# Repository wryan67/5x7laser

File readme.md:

## 5x7 laser gun

This lasergun can be produced using 5" x 7" sheets of plastic or basswood.

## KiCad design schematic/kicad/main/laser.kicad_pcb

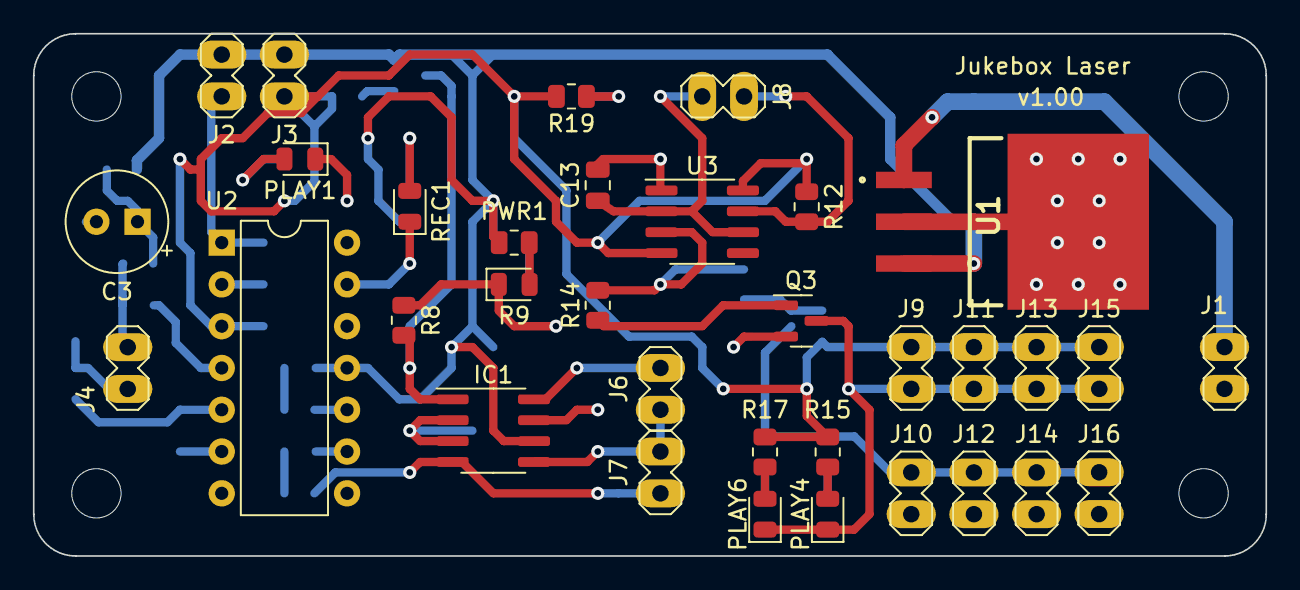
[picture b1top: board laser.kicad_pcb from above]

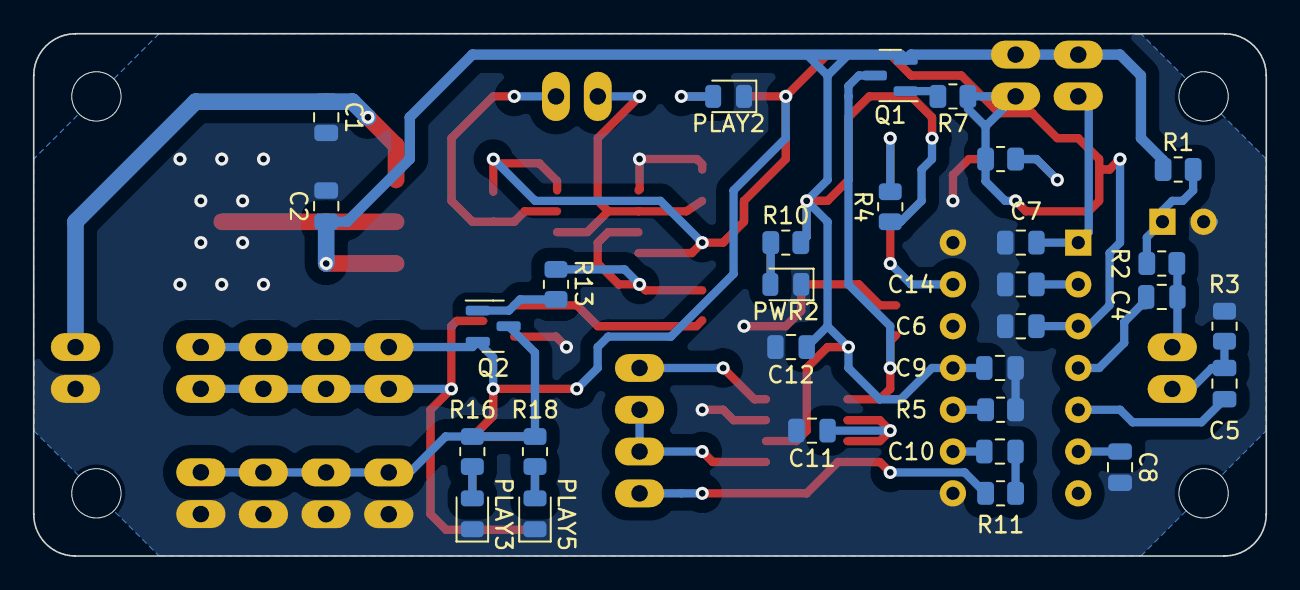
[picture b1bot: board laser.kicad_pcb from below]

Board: 2 copper layers, 74.9 x 31.8 mm, 64 parts (30 on the bottom side), 38 nets.

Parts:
C1: 334; C_0805_2012Metric
C2, C4, C5, C9: 104; C_0805_2012Metric
C3: 220 µF; CP_Radial_Tantal_D6.0mm_P2.50mm
C6, C7, C14: 102; C_0805_2012Metric
C8: 475; C_0805_2012Metric
C10: 394; C_0805_2012Metric
C11, C12: 105; C_0805_2012Metric
C13: 106; C_0805_2012Metric
IC1: LM4871MX_NOPB; LM4871
J1: Power; PinHeader_1x02_P2.54mm_Vertical_Wide
J2: Rec; PinHeader_1x02_P2.54mm_Vertical_Wide
J3: Play; PinHeader_1x02_P2.54mm_Vertical_Wide
J4: Mic; PinHeader_1x02_P2.54mm_Vertical_Wide
J6: Speaker; PinHeader_1x02_P2.54mm_Vertical_Wide
J7, J8: 100k pot; PinHeader_1x02_P2.54mm_Vertical_Wide
J9, J10, J11, J12, J13, J14, J15, J16: LED; PinHeader_1x02_P2.54mm_Vertical_Wide
PLAY1, PLAY2: Blue; LED_0805_2012Metric
PLAY3, PLAY4, PLAY5, PLAY6: Yellow; LED_0805_2012Metric
PWR1, PWR2: Green; LED_0805_2012Metric
Q1, Q2: 2PB709AXL; SOT-23
Q3: PMBT2222A; SOT-23
R1, R4, R6, R9, R10, R12, R19: 1k; R_0805_2012Metric
R2, R3: 4.7k; R_0805_2012Metric
R5: 80k; R_0805_2012Metric
R7, R13, R14: 100k; R_0805_2012Metric
R8, R11: 10k; R_0805_2012Metric
R15, R16, R17, R18: 200 Ω; R_0805_2012Metric
REC1: Red; LED_0805_2012Metric
U1: ua7805; ua7805-KTT-_R-PSFM-G3_
U2: ISD1820
U3: NE555D; SOIC-8_3.9x4.9mm_P1.27mm

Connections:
+5v: C2.1, C9.1, C12.1, IC1.6 (VDD), J2.2, J3.2, Q1.2 (E), R1.1, R4.1, R9.2, R10.2, U1.3 (OUTPUT), U2.11 (Vcc)
+9v: C1.1, J1.2, U1.1 (INPUT)
/Amplifier/SPK+: IC1.5 (VO1), J6.2, J7.1
/Amplifier/SPK-: IC1.8 (VO2), J6.1
/Jukebox/AGC: C8.1, U2.6 (AGC)
/Jukebox/M+: C4.1, U2.4 (MIC(+))
/Jukebox/M-: C5.1, U2.5 (MIC(-))
/Jukebox/PLAY_E: C14.1, U2.2 (PLAY_E)
Flasher Speed: J8.1, R12.2, U3.7 (DIS)
GND: C1.2, C2.2, C3.2, C6.2, C7.2, C8.2, C9.2, C11.2, C12.2, C13.2, C14.2, IC1.7 (GND), J1.1, J10.2, J12.2, J14.2, J16.2, PLAY1.1 (K), PLAY2.1 (K), PLAY3.1 (K), PLAY5.1 (K), PWR1.1 (K), PWR2.1 (K), Q3.2 (E), R3.2, R5.2, R8.1, U1.2 (COMMON_1), U1.4 (COMMON_2), U2.8 (VSSA), U2.14 (VSSD), U3.1 (GND)
Mic(+): C4.2, J4.2, R2.2
Mic(-): C5.2, J4.1, R3.1
unnamed: C3.1, R1.2, R2.1
unnamed: C10.2, R11.2
unnamed: C11.1, IC1.2 (BYPASS), IC1.3 (+IN)
unnamed: C13.1, J8.2, U3.2 (TR), U3.6 (THR)
unnamed: J10.1, J12.1, J14.1, J16.1, Q2.3 (C), R16.2, R18.2
unnamed: J9.2, J11.2, J13.2, J15.2, PLAY4.1 (K), PLAY6.1 (K), Q3.3 (C)
unnamed: PLAY1.2 (A), R6.1
unnamed: PLAY2.2 (A), R19.1
unnamed: PLAY3.2 (A), R16.1
unnamed: PLAY4.2 (A), R15.1
unnamed: PLAY5.2 (A), R18.1
unnamed: PLAY6.2 (A), R17.1
unnamed: PWR1.2 (A), R9.1
unnamed: PWR2.2 (A), R10.1
unnamed: Q1.1 (B), R7.2
unnamed: Q2.1 (B), R13.2
unnamed: Q3.1 (B), R14.1
unnamed: R4.2, REC1.2 (A)
unnamed: REC1.1 (K), U2.13 (RECLED)
unnamed: R5.1, U2.10 (ROSC)
unnamed: R13.1, R14.2, U3.3 (Q)
PLAY: C6.1, J3.1, J9.1, J11.1, J13.1, J15.1, Q2.2 (E), R6.2, R7.1, R12.1, R15.2, R17.2, R19.2, U2.3 (PLAY_L), U3.4 (R), U3.8 (VCC)
REC: C7.1, J2.1, U2.1 (REC)
SPK(+): C10.1, U2.9 (SPK(+))
Shutdown: IC1.1 (SHUTDOWN), Q1.3 (C), R8.2
VOL(-): IC1.4 (-IN), J7.2, R11.1

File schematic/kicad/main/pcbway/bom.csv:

"Id";"Designator";"Footprint";"Quantity";"Designation";"Supplier and ref";
1;"REC1";"LED_0805_2012Metric";1;"Red";;;
2;"J10,J16,J12,J9,J15,J11,J14,J13";"PinHeader_1x02_P2.54mm_Vertical_Wide";8;"LED";;;
3;"R8,R11";"R_0805_2012Metric";2;"10k";;;
4;"C13";"C_0805_2012Metric";1;"106";;;
5;"R17,R15,R18,R16";"R_0805_2012Metric";4;"200 Ω";;;
6;"J4";"PinHeader_1x02_P2.54mm_Vertical_Wide";1;"Mic";;;
7;"PWR1,PWR2";"LED_0805_2012Metric";2;"Green";;;
8;"IC1";"LM4871";1;"LM4871MX_NOPB";;;
9;"J1";"PinHeader_1x02_P2.54mm_Vertical_Wide";1;"Power";;;
10;"C3";"CP_Radial_Tantal_D6.0mm_P2.50mm";1;"220 µF";;;
11;"U3";"SOIC-8_3.9x4.9mm_P1.27mm";1;"NE555D";;;
12;"J2";"PinHeader_1x02_P2.54mm_Vertical_Wide";1;"Rec";;;
13;"R14,R7,R13";"R_0805_2012Metric";3;"100k";;;
14;"J3";"PinHeader_1x02_P2.54mm_Vertical_Wide";1;"Play";;;
15;"PLAY6,PLAY4,PLAY5,PLAY3";"LED_0805_2012Metric";4;"Yellow";;;
16;"U2";"ISD1820";1;"ISD1820";;;
17;"PLAY1,PLAY2";"LED_0805_2012Metric";2;"Blue";;;
18;"R12,R19,R9,R4,R1,R6,R10";"R_0805_2012Metric";7;"1k";;;
19;"J6";"PinHeader_1x02_P2.54mm_Vertical_Wide";1;"Speaker";;;
20;"U1";"ua7805-KTT-_R-PSFM-G3_";1;"ua7805";;;
21;"J7,J8";"PinHeader_1x02_P2.54mm_Vertical_Wide";2;"100k pot";;;
22;"Q3";"SOT-23";1;"PMBT2222A";;;
23;"C9,C2,C5,C4";"C_0805_2012Metric";4;"104";;;
24;"Q2,Q1";"SOT-23";2;"2PB709AXL";;;
25;"R2,R3";"R_0805_2012Metric";2;"4.7k";;;
26;"C1";"C_0805_2012Metric";1;"334";;;
27;"C12,C11";"C_0805_2012Metric";2;"105";;;
28;"C7,C6,C14";"C_0805_2012Metric";3;"102";;;
29;"C8";"C_0805_2012Metric";1;"475";;;
30;"C10";"C_0805_2012Metric";1;"394";;;
31;"R5";"R_0805_2012Metric";1;"80k";;;

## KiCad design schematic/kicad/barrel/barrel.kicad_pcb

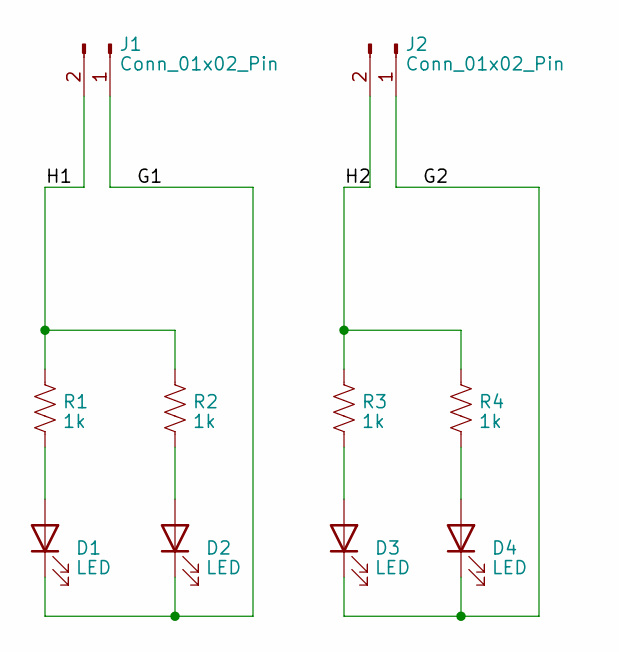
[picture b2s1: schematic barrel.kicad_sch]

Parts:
D1, D2, D3, D4: LED; LED_0805_2012Metric
J1, J2: Conn_01x02_Pin; PinHeader_1x02_P2.54mm_Vertical_Wide
R1, R2, R3, R4: 1k; R_0805_2012Metric

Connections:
/G1: D1.1 (K), D2.1 (K), J1.1
/G2: D3.1 (K), D4.1 (K), J2.1
/H1: J1.2, R1.1, R2.1
/H2: J2.2, R3.1, R4.1
unnamed: D1.2 (A), R1.2
unnamed: D2.2 (A), R2.2
unnamed: D3.2 (A), R3.2
unnamed: D4.2 (A), R4.2

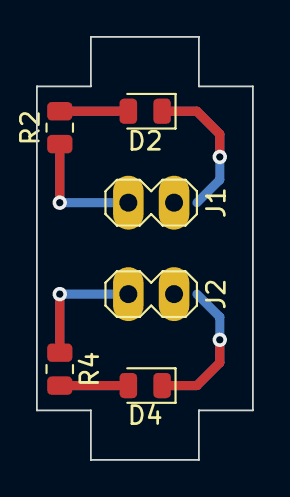
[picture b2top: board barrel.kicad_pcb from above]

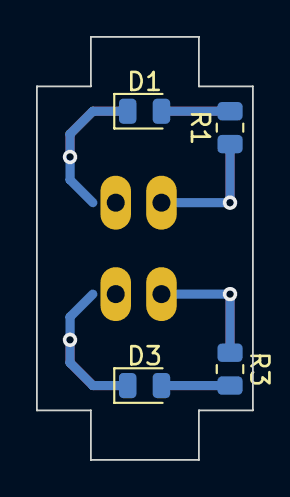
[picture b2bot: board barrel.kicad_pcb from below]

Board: 2 copper layers, 12.0 x 23.5 mm, 10 parts (4 on the bottom side), 8 nets.

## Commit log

2023-05-02 5x7laser
